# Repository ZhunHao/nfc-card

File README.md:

# NFC energy-harvesting business cards

Two battery-free PCB business cards. Tap one on a phone and its NFC field powers an
ATtiny1616 that animates 20 Charlieplexed red LEDs. There's no battery and no button.

The Orbit card on the back of an Android phone, running only on power harvested from the NFC
field: an ISS pass, the ground stations, then the 2,000 km pass.

The Terminal card hasn't been built yet, so these are the KiCad renders of both designs:

| C1 Orbit | B3 Terminal |
| --- | --- |
|  |  |
|  |  |

- **C1 Orbit**: Earth's limb, the ISS orbit (420 km) and the top of LEO (2,000 km) at true
  scale (1 mm ≈ 80 km). LEDs trace an ISS pass, light three ground stations, then run the
  2,000 km pass.
- **B3 Terminal**: a macOS Terminal window running `ping`. Each output line gets a status LED,
  and a progress bar fills along the bottom.

The phone number is left off the committed boards; see [Your own contact details](#your-own-contact-details).

## Inspiration and credit

This project is directly inspired by **Wilson Harper's
[NFC Energy-Harvesting PCB Business Card with an MCU](https://wilsonharper.net/projects/businesscard/)**
([repo](https://github.com/WiHarper/nfc-card)). His write-up showed that an NXP NTAG I2C Plus
can harvest enough power from a phone to run an ATtiny and Charlieplexed LEDs on a card-sized
board. Several decisions here follow his card directly:

- the **soft-start reservoir**: a large capacitor charged through a resistor, then switched
  in by a P-FET under MCU control, so VOUT stays inside the NTAG's 220 nF limit at start-up;
- a perimeter coil with **no ground plane** and LED routing that never closes a loop;
- **UPDI / VCC / GND pads at 0.1" pitch** on the back for a pogo-pin clip, with a TVS diode on
  UPDI, programmed with an Adafruit UPDI Friend;
- thin (≈ 0.8 mm) ENIG boards, assembled by JLCPCB.

Read his write-up first. It explains the core ideas better than this repo does. What this
repo adds is two new card designs on an ATtiny1616 (VQFN-20), scripted KiCad layouts,
interrupt-driven LED scanning with brown-out-aware power tiers, and a bring-up log that
includes iPhone behaviour.

## Hardware

| | |
| --- | --- |
| NFC / harvester | NXP NTAG I2C Plus NT3H2111 (VOUT energy harvesting) |
| MCU | Microchip ATtiny1616-MNR, VQFN-20 3 × 3 mm |
| LEDs | 20 × red 0603, Charlieplexed on 5 GPIOs, 100 Ω per line |
| Antenna | 4-turn perimeter coil, 0.50 mm gaps, tuned with the NTAG's 50 pF |
| Board | ID-1 (85.6 × 54 mm), 0.8 mm FR-4, 2 layers, black mask, ENIG |
| Programming | UPDI pads TP1–TP3 on the back (UPDI / VCC / GND, 2.54 mm pitch) |

The two cards share one circuit, and `scripts/check.sh` checks it: each schematic's netlist
must match `fab/reference/card-netlist.xml`.

**Status (2026-11):** Orbit has been built (JLCPCB order Y8) and brought up. On Android the
full animation runs on harvested power. iOS only powers the field in short polls, so an
iPhone tap gives a single LED blink and opens the URL. See
[docs/bringup](docs/bringup/2026-11-08-orbit-first-cards.md).

## Repository layout

```
hardware/   KiCad 10 projects (orbit/, terminal/), shared symbol + footprint library (lib/),
            and the Python builders that generate each board's placement, routing and silk
firmware/   bare-metal C for the ATtiny1616: shared core in src/, one animation per board in
            boards/, host tests in tests/, programming script in tools/
scripts/    checks (ERC/DRC/parity/netlist/coil loops/thickness), antenna generator, JLC
            DFM clean-up, fab export (single card and two-card panel)
sim/        LTspice decks and coil inductance estimates
docs/       design concepts, NFC tag setup, panel quotes, bring-up log
gallery/    photos of the built Orbit card and renders of both designs
```

## Build and check

You need KiCad 10 (`kicad-cli` and its bundled Python), Python 3, a host C compiler and
avr-gcc 14.3.0 (the version the ISR timing was audited against).

```bash
AVR_CC=/path/to/avr-gcc-14.3.0 ./scripts/check.sh
```

This runs ERC, DRC, schematic parity, board thickness, coil-loop and netlist checks for every
board under `hardware/`, plus the firmware host tests and AVR builds for every animation.

Regenerate a board after editing its builder (run it with KiCad's Python):

```bash
/Applications/KiCad/KiCad.app/Contents/Frameworks/Python.framework/Versions/Current/bin/python3 hardware/orbit/build_orbit.py
```

Export a JLCPCB package (gerbers, BOM, CPL with JLC rotation offsets, renders). It goes to
`fab/<board>-v2/`, which is not committed:

```bash
python3 scripts/export-card.py orbit
```

Flash a card over UPDI (Adafruit UPDI Friend plus a 0.1" pogo clip). See
[firmware/README.md](firmware/README.md):

```bash
firmware/tools/program-card.sh orbit-01
```

The NTAG is written from a phone (NFC Tools or NXP TagWriter). A blank NT3H2111 has to be
formatted first; see [docs/nfc-tag.md](docs/nfc-tag.md).

## Your own contact details

The card backs print a name, title, email and website. To keep a phone number out of the
repo, the committed boards leave it off, and the builders only add it when you pass a
private contact file:

```bash
cp contact.example.json contact.local.json   # gitignored; put your number in it
python3 scripts/export-card.py orbit --contact contact.local.json
```

That rebuilds a private copy under `build/personal/` and exports gerbers from that copy. The
boards under `hardware/` are not touched. To make the cards your own, change the name, email
and site in `hardware/*/build_*.py`.

## License

- Hardware (`hardware/`, `fab/reference/`, `sim/`):
  [CERN-OHL-S-2.0](LICENSES/CERN-OHL-S-2.0.txt)
- Firmware and scripts (`firmware/`, `scripts/`, `docs/design/data/`):
  [GPL-3.0-or-later](LICENSES/GPL-3.0-or-later.txt)

These are the licences of [Wilson Harper's card](https://github.com/WiHarper/nfc-card), which
inspired this one. See [LICENSE.md](LICENSE.md).

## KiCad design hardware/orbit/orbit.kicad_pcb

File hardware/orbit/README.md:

# C1 Orbit to scale

Earth's limb and two orbits at true scale on an ID-1 card: Earth R = 80 mm centred at
concept (43, 118), so 1 mm ≈ 79.64 km. ISS orbit r = 85.274 mm (420 km), upper orbit
r = 105.114 mm (2,000 km, top of LEO). Every arc, bus and LED is concentric with Earth.
Concept coordinates are mm from the card's top-left; KiCad = concept + 100.

Rev B electronics: the
NTUAS circuit with U2 as ATtiny1616-MNR (VQFN-20 3 × 3 mm), a UPDI ESD diode D21, a soft-start
reservoir (Q1, R7, R8, C4), test pads on the back and antenna option A. U1, C1, C2 and the U1
end of the LA/LB routing are the NTUAS card's; the LA feed to the coil is rebuilt (see Routing).
Everything else on the board is generated by `build_orbit.py` (KiCad 10 Python, idempotent):

```bash
/Applications/KiCad/KiCad.app/Contents/Frameworks/Python.framework/Versions/Current/bin/python3 hardware/orbit/build_orbit.py
```

## LED mapping

LED index k is D[k+1]: anode CP[k/4], cathode CP[c], c = (k%4) < (k/4) ? k%4 : k%4+1.
Positions are listed left to right. `firmware/boards/orbit/animation.c` uses the same order.

| Row | x (concept mm) | Ref (index k) |
| --- | --- | --- |
| ISS, r 85.274 | 12, 19.8, 27.6, 35.4, 43.2, 51, 58.8, 66.6, 74.4 | D2 (1), D3 (2), D1 (0), D4 (3), D6 (5), D7 (6), D8 (7), D5 (4), D9 (8) |
| 2,000 km, r 105.114 | 11, 19.5, 28, 36.5, 45, 53.5, 62, 70.5 | D10 (9), D13 (12), D14 (13), D15 (14), D17 (16), D18 (17), D19 (18), D20 (19) |
| Ground stations, limb + 2.6 | 27.6, 43, 66 | D11 (10), D16 (15), D12 (11) |

The station LEDs sit under the ISS LEDs at x = 27.6, 43.2 and 66.6, which light them in the animation.

## Deviations from the concept

- **Ground station x = 20 moved to x = 27.6** (still on the limb, 2.6 mm inside it). At x = 20 it
  landed on U1/C2 at the antenna feed. 27.6 puts it under an ISS LED like the other two.
- All LEDs are rotated tangent to their orbit (concept draws them axis-aligned).
- Labels are raised from 0.95 to 1.0 mm (JLCPCB standard minimum, 0.15 mm stroke) in KiCad's
  stroke font, not JetBrains Mono. Letter spacing is not available except for `E A R T H`,
  which is set letter by letter. `ISS · 420 km` starts at x = 43.5 (concept 47) to stay off the
  routing trunk; `2,000 km · TOP OF LEO` sits 2.4 mm above its arc (concept 1.4) because the
  wider stroke font would otherwise cover the LEDs at x = 36.5 and 45.
- **LED cathode dots** (after order Y8): a 0.4 mm silk dot beside each LED's pad 1 (the
  cathode), on the side away from its bus stubs (outward on the ISS row, inward on the
  2,000 km row and the stations), 0.27 mm clear of the pad. The library LED outline sits
  0.1 mm from the pads, so the 0.25 mm silk cut-back removed it and Y8 shipped with no LED
  polarity mark, which led JLC to ask for a polarity check. A dot past the pad end would land
  on the orbit line and look like an orbit dot. The station chevrons are 0.35 mm lower than
  the concept (tip 1.2 mm below the LED centre) to clear the dots.
- Silk lines are all ≥ 0.15 mm. The concept's faint 0.09 mm rings and meridians are drawn
  dashed at 0.15 mm instead of at reduced opacity. Silk stops 0.25 mm short of pads.
- MCU block (concept mm): U2 (VQFN-20) at (69.5, 23.0), 90°, pin 1 bottom-left. R1–R5 stay in a
  column at x = 61.8 by the trunk (y = 23.8 … 27.8, PA1 … PA5). C3 sits under U2's VCC/GND pins at
  (69.7, 26.7), JP1 at (61.2, 30.6), R6 above U2 at (66.7, 20.6). The soft-start sits right of U2:
  R8 (74.2, 21.3), R7 (74.2, 22.3), Q1 (73.9, 23.6), C4 (72.75, 22.6). `LIFT JP1 TO FLASH` from
  the NTUAS card is dropped; JP1 is labelled.
- **Test pads on the back** (rev B): TP1/TP2/TP3 (**UPDI / VCC / GND**, VCC in the middle) are
  1.5 mm pads on B.Cu in a vertical column at 2.54 mm pitch, x = 77.5, y = 7.8 / 10.34 / 12.88,
  for a 0.1" pogo clip. Seen from the back they sit top-left, above the name, with mirrored
  B.SilkS labels (1.0 mm tall, 0.8 mm glyphs) aligned with the contact block. Each pad is fed by
  a via 1.25 mm to its left, never in the pad. The front TP labels are gone.
- D21 (UPDI TVS) sits on the front directly behind TP1, at (77.55, 8.25); its GND pad runs down
  to TP3's via.
- Back: `TAP TO CONNECT` and its glyph moved 2 mm toward the centre to clear the antenna band.
- Back: the two TLE lines keep the 1.0 mm height but use 0.62 mm-wide glyphs, so they run
  about 39 mm like the concept's monospace (37.6 mm) instead of 62 mm. JLC's line gap is still met.

## Routing

Each orbit row has five concentric B.Cu bus arcs, one per Charlieplex net (ISS buses inside the
ISS row, 2,000 km buses outside its row, pitch 0.85 mm). Every LED pad drops a short radial F.Cu
stub to a via on its net's bus. One radial F.Cu trunk (through the ISS orbit at x = 55, between
LEDs) joins both bus sets; B.Cu branches tap it to R1–R5. The stations share the ISS buses: the
ISS LED above each station only uses buses outside both of the station's, so their stubs never
meet. VOUT and GND leave U1/C2 on B.Cu arcs inside Earth (r ≈ 78 and 76.5 mm) and ride the trunk
up to JP1 and the MCU. No autorouter was used; DRC (error severity) is clean with no unconnected
items and no parity issues.

**MCU block fan-out (VQFN-20, 0.4 mm pitch).** Escapes are 0.15 mm straight out of each pad.
PA1 (pin 20, left side) and PA2/PA3 (pins 1/2, bottom side) run to R1–R3 on F.Cu as nested
L-shapes. PA4/PA5 (pins 5/6) drop to vias beside the package and pass under the block on B.Cu to
vias next to R4/R5. GND (pin 3) is tied to the exposed pad by a short track inside the body
(no ground plane on this card) and, with VCC (pin 4), runs straight down into C3. UPDI (pin 19)
goes up through R6 and over the top of U2; SS_GATE (pin 15) runs alongside to R8 and Q1's gate.
VCC goes JP1 → C3 → a spine up the right side to TP2, with the soft-start parts and Q1's source
stubbed onto it. GND runs on B.Cu directly under that VCC rail and spine (a broadside pair, so
the VCC/GND loop closed by C3 and C4 encloses almost nothing) up to TP3, with a branch to C4.

**Antenna feed (option A).** The new coil's outer pad (LA) is at (120.0, 151.53) and its inner
pad (LB) at (114.4, 147.33), KiCad mm. The NTUAS LA via at (120.0, 150.7) would sit inside coil
turn 2 (same net, so DRC is silent, but it bypasses part of the coil), so it is gone: LA leaves
U1 as before, runs down B.Cu at x = 115.8 to y = 152.9 (outside the coil), across to a via at
(120.0, 152.9) and back up F.Cu to the pad. LB drops from (114.7, 146.58) to its pad at
(114.4, 147.33). The builder rebuilds the whole LA/LB set each run. The coil band is wider now
(2.0–7.1 mm from the edge, was ~3.8–6.5 on NTUAS). Widening the gaps to 0.50 mm (2026-10-27)
moved the inner edge from 6.5 to 7.1 mm, but no LED, bus or silk moved: the closest other-net
F.Cu copper is the TP1 via at (176.25, 107.8), about 0.4 mm away. TP1–TP3 themselves are on
B.Cu, under the inner turn.

## Manufacturing notes

Same as the NTUAS card: black
mask, ENIG, top-side assembly, but **0.8 mm** thick (NTUAS: 1.0 mm); set PCB Thickness to 0.8
in the JLC quote. **36 fitted parts** (the NTUAS 31 plus D21, Q1, R7, R8,
C4); C1 (not fitted), L1 (copper) and TP1–TP3 (bare pads on the back) are not assembled. U2 is
the VQFN-20 ATtiny1616-MNR (LCSC C507118) at 90° here. `scripts/export-card.py` corrects U2
(-90°) and Q1 (180°) for JLC's library, as checked on the Terminal card in JLCONE on 2026-10-28.
Orbit's own placement preview was checked the same day (see Ordering below).

Physical validation (NFC range, LED brightness, harvested power) is still unproven on the NTUAS
card and inherited here.

## Ordering (JLCPCB)

The first batch (Y8, 2026-10-28) was 20 PCBs with 15 assembled, about US$141 before shipping.

- **PCB:** 0.8 mm FR-4, black mask, ENIG, 1 oz, tented 0.3 mm vias, order number removed,
  Confirm Production File on.
- **Assembly:** Standard PCBA, top side, JLC adds and removes the edge rails, Confirm Parts
  Placement on. Upload the `bom.csv` and `cpl.csv` from `scripts/export-card.py`, which already
  apply the U2 and Q1 rotation offsets.
- **Placement preview:** every LED needs JLC's "−" on pad 1 (the cathode); U1, U2 and Q1 need
  their pin-1 dots on pad 1. D21 is bidirectional.
- Y8 had no LED polarity marks (see "LED cathode dots"), so JLC's engineer revised the LED
  placement and asked for a polarity check. The current boards have the marks.
- Approve the placement within 72 h (JLC auto-confirms after that), then flash the firmware
  over TP1–TP3.

## Bring-up (2026-11-08)

Full log: `docs/bringup/2026-11-08-orbit-first-cards.md`.

- **R6 is too high for the UPDI Friend.** With R6 = 4.7 kΩ the chip's reply never pulls the
  Friend's line (1 kΩ pull-up) below about 2.7 V, so avrdude fails at link initialization. Bridge
  R6 to program; it can stay bridged (D21 still clamps TP1). **Fixed in the design
  (2026-11-08): R6 is now 0 Ω** (UNI-ROYAL 0402WGF0000TCE, LCSC C17168, JLC basic) in the
  schematic, the board and `fab/reference/card-netlist.xml`. No resistor is needed on the card: the UPDI Friend already has 1 kΩ in series with its TX, it powers the card from the same 3 V supply, and D21 clamps static on TP1. Every setup known to work has none (R6 bridged on Y8, Wilson Harper's card).
  470 Ω (SpenceKonde's value for programmers that drive UPDI directly) was tried first
  and dropped untested: a divider estimate put the low level near 1.1 V against the
  Friend's 1 kΩ. The 0402 pads stay, so a resistor can be fitted for another programmer.
  Only future orders get it: the 15 assembled Y8 cards have 4.7 kΩ and still
  need R6 bridged.
- On card 2 with R6 bridged: signature `0x1e9421`, fuses set, all 20 LEDs and the Orbit
  animation verified on 3.3 V programmer power. The tag still reads with JP1 fitted.
- Harvested power starts the MCU and passes the VLM check with the card on the back of an
  iPhone, without C1. The iPhone field lasts only about 30–65 ms per tap, so the animation
  (100 ms qualification, 800 ms fade-in) does not show there; firmware now flashes D16 at
  power-up so each iPhone poll gives a blink. On Android the full animation runs.
- Card 1 was reverse-powered several times by a cable whose colours differ from Adafruit's
  guide, and has not been rechecked.

## Pre-order checks (2026-10-26)

Estimates and design-file checks only. None replaces tapping a phone on an assembled card.

**Antenna (rev B: option A).** L1 is now `nfc-card:NFC_Antenna_Rect_ID1_4turn_W090`: 4 turns
at a 2.0 mm inset, 0.90 mm track, **0.50 mm gap** (1.40 mm pitch). FastHenry
(`sim/fasthenry_coil.py`, skin effect resolved) gives **2.37 µH at 13.56 MHz**, so 14.63 MHz at
the NTAG's 50 pF (13.82–15.59 MHz over 44–56 pF), aiming high so C1 (not fitted) can tune it
down after a NanoVNA check: 14.41 / 14.17 / 13.87 MHz with C1 = 1.5 / 3.3 / 5.6 pF. Area ×
turns is 138 cm². Until 2026-10-27 the gap was 0.30 mm on AN11276's 2.39 µH, but FastHenry gives
that coil 2.49 µH: 14.26 MHz at 50 pF and 13.48 MHz at 56 pF, under the carrier with no fix,
since C1 only lowers it. `sim/coil_inductance.py` (Neumann integrals over the routed copper)
agrees, 2.388 µH at low frequency against FastHenry's 2.368 µH at 13.56 MHz. Board parasitics are
not in either number and will pull the frequency down a little. The NTUAS coil's estimate below is kept for reference:
Mohan et al. (IEEE JSSC 34(10), 1999), 77.6 × 45.98 mm outer, 4 turns, 0.35/0.35 mm: modified
Wheeler 2.41 µH → 14.49 MHz, current sheet 2.84 µH → 13.35 MHz, which could sit under 13.56 MHz.

**Copper inside the coil.** `scripts/check_loops.py` (run by `check.sh`) finds no closed copper
loop in any of the 19 routed nets on rev B. The supply loops close through capacitors, which are
near-shorts at 13.56 MHz. The always-closed C2 → JP1 → C3 loop encloses 30.6 mm² (rev A:
36.7 mm²), about 0.9 % of a mean rev B coil turn (~3,500 mm²). The largest supply loop is
C4 → Q1 → JP1 → U1 at 45.6 mm², closed once the firmware turns Q1 on. The gate fails any
supply loop over 100 mm². Lit-LED drive loops reach 102.8 mm² (D3), but an off LED is open at
RF and a lit one has about 400 Ω in series, so they are reported, not gated. The upper B.Cu bus
is 1.6 mm inside the innermost turn at its closest.

**Harvest power budget, LTspice** (`sim/harvest*.cir`). NTAG VOUT is modelled as a current source
clamped near 3.3 V (NXP datasheet Vout,max). C2 + C3 = 200 nF. The MCU is a 0.6 mA load, which is
pessimistic: the datasheet gives 8 MHz active at 3 V as 2.2 mA typical, 3.5 mA max, so 1 MHz scales
to about 0.3–0.45 mA. Each GPIO is 100 Ω (assumed; Microchip publishes only curves). The scan pulse
is the firmware's 62 µs per 250 µs slot. The LED model is fitted to KT-0603R at 2.0 V (typ) and
2.4 V (max) at 20 mA. Minimum VCC with at most two LEDs lit, as this animation runs:

| Harvested current | 0.3 mA | 0.5 mA | 0.75 mA | 1 mA | 2 mA | 5 mA |
| --- | --- | --- | --- | --- | --- | --- |
| VCC min, typical LED | 1.00 V | 1.61 V | 2.06 V | 2.41 V | 2.66 V | 3.21 V |
| VCC min, 2.4 V LED | 1.00 V | 1.66 V | 2.25 V | 2.61 V | 2.86 V | 3.24 V |
| LED peak current, typical | – | 0.2 mA | 2.0 mA | 3.5 mA | 3.7 mA | 3.8 mA |

Rev B adds the soft-start reservoir (C4 10 µF behind R7 2.2 kΩ, bypassed by Q1 once the
firmware latches it), which these 200 nF runs do not model; see `sim/vout_reservoir.cir` at the
repo root for its effect on ripple, hold-up and startup.

BODLEVEL0 is 1.7–2.0 V, so the card needs about **0.75–1 mA** from the phone to run. NXP's
typical figure is 5 mA at 2 V; the MCU, not the LEDs, dominates the load. Even with every slot
lit (`harvest.cir`), 1.5 mA holds VCC at or above 2.5 V.

**Brightness is the weaker margin.** The fixed scan gave each LED one 250 µs slot per 5 ms frame
at 62 µs on (1.25 % duty), about 20–46 µA from 2–3.8 mA peaks. Orbit and Terminal now use shared
slots (`firmware/docs/timing.md`): the lit LEDs share 6 slots, so one lit LED is on 7.4 % of the
time (about 150–280 µA) and two are on 3.7 % each (about 75–140 µA). Six lit slots is well under
the every-slot-lit case above. Whether that reads as clearly lit can only be judged on a real card.

**Gerbers (rev A export; redo for rev B).** The zip re-read: 9 layers plus a job file, 1.0 mm, 2 layers, 85.65 × 54.03 mm
including the outline stroke. The drill file has 69 × 0.3 mm holes, matching the 69 vias. B.Mask
and B.Paste are empty (single-sided). Rev B has 76 vias and opens B.Mask for the three test
pads, so these counts change at the next export. `scripts/jlc_dfm.py` (run before saving) widens all
silkscreen, library outlines included, to 0.16 mm, cuts it back 0.25 mm from every pad and hole,
gives U1/U2/Q1 a 0.02 mm mask margin and every via a 0.65 mm pad. The UPDI run over R6 moved up
0.2 mm (concept y 19.4) to clear R6's mask opening. JLCDFM (2026-10-28) then reports no danger or
warning items on the PCB; the SMT notes are as on Terminal (see its README).

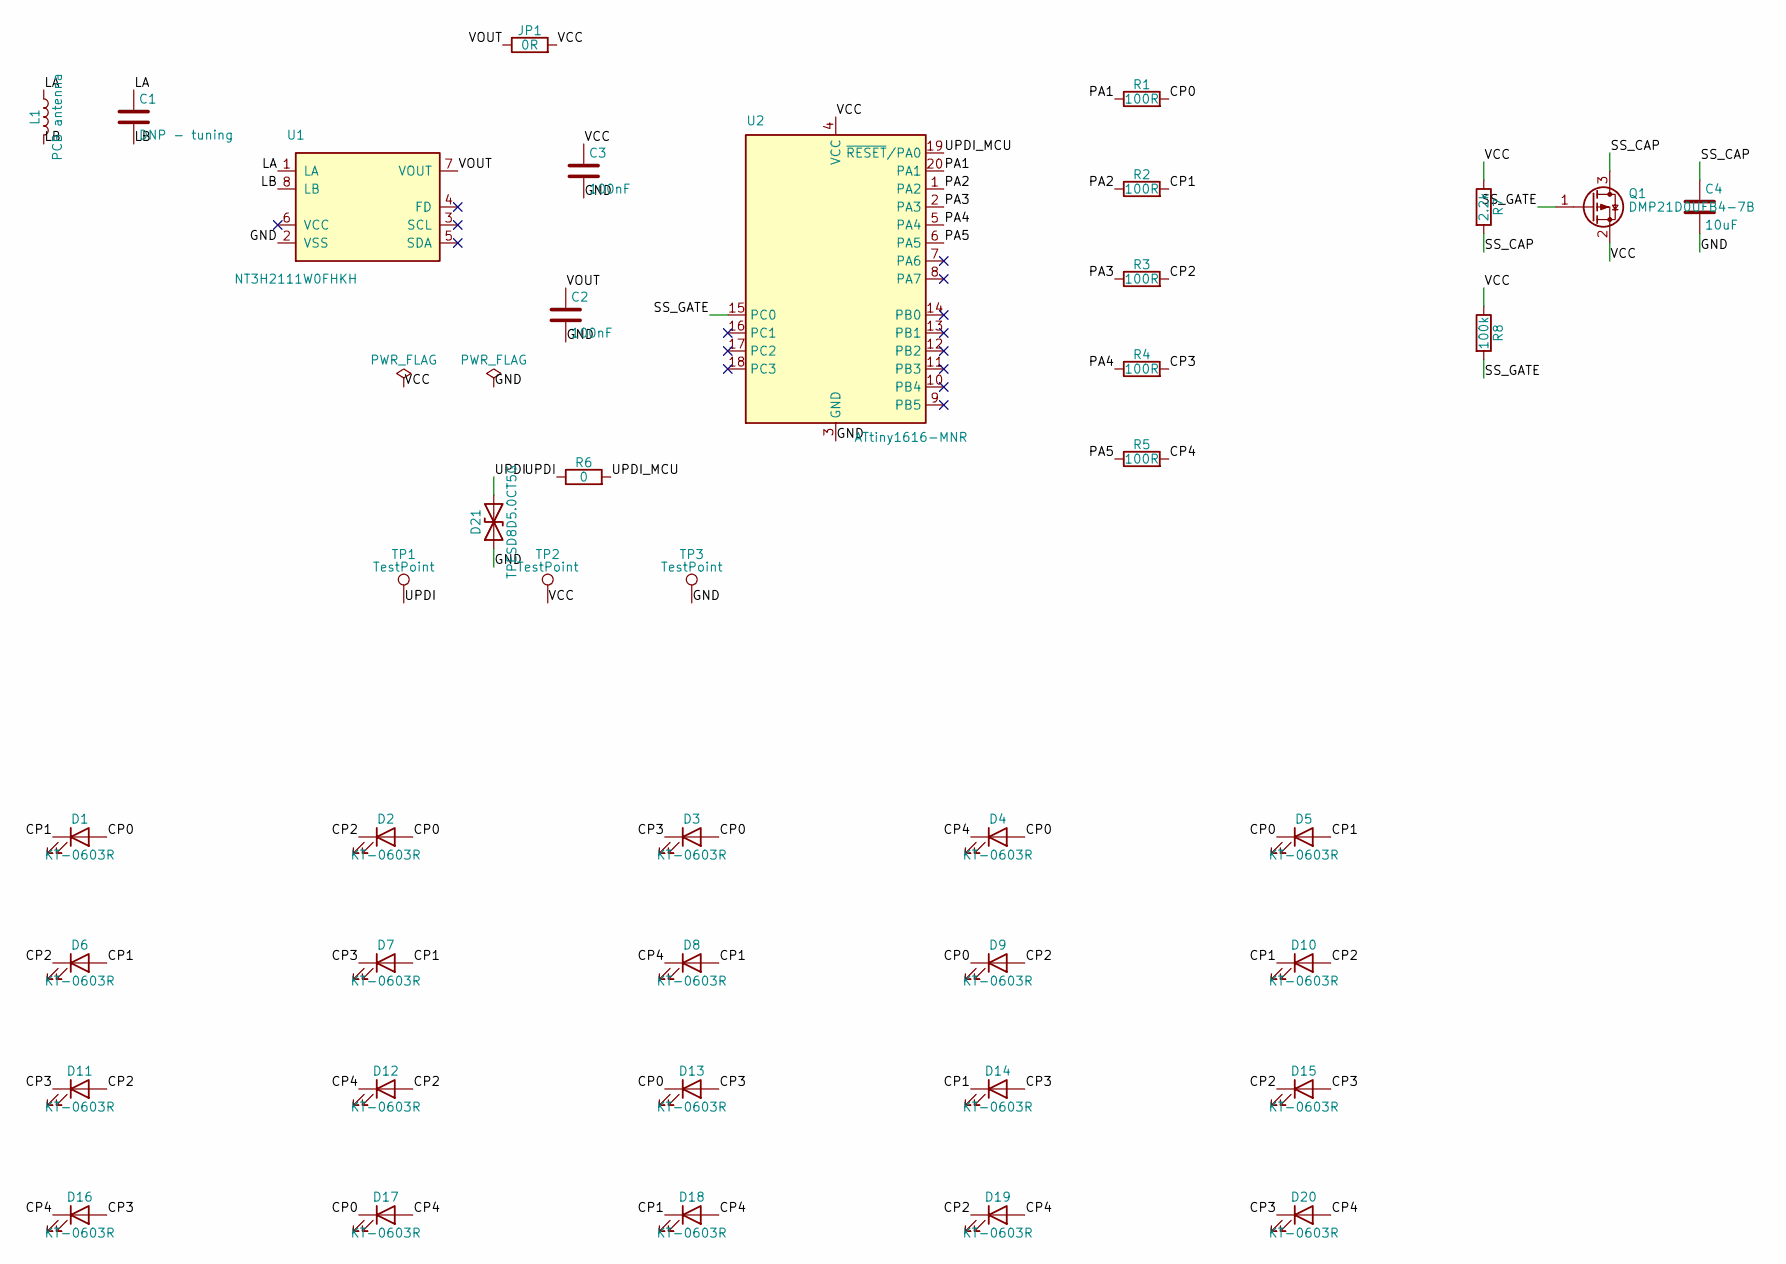
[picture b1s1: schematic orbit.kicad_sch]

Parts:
C1: DNP - tuning; C_0402_1005Metric
C2, C3: 100nF; C_0402_1005Metric; LCSC C1525
C4: 10uF; C_0402_1005Metric; LCSC C15525
D1, D2, D3, D4, D5, D6, D7, D8, D9, D10, D11, D12, D13, D14, D15, D16, D17, D18, D19, D20: KT-0603R; LED_0603_1608Metric; LCSC C2286
D21: TPESD8D5.0CT5G; D_SOD-882; LCSC C2827720
JP1: 0R; R_0603_1608Metric; LCSC C21189
L1: PCB antenna; NFC_Antenna_Rect_ID1_4turn_W090
Q1: DMP21D0UFB4-7B; Diodes_DFN1006-3; LCSC C155329
R1, R2, R3, R4, R5: 100R; R_0402_1005Metric; LCSC C25076
R6: 0; R_0402_1005Metric; LCSC C17168
R7: 2.2k; R_0402_1005Metric; LCSC C25879
R8: 100k; R_0402_1005Metric; LCSC C25741
TP1, TP2, TP3: TestPoint; TestPoint_Pad_D1.5mm
U1: NT3H2111W0FHKH; XQFN-8_1.6x1.6mm_P0.5mm_NXP_SOT902-3; LCSC C710403
U2: ATtiny1616-MNR; QFN-20-1EP_3x3mm_P0.4mm_EP1.65x1.65mm; LCSC C507118

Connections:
/CP0: D1.2 (A), D2.2 (A), D3.2 (A), D4.2 (A), D5.1 (K), D9.1 (K), D13.1 (K), D17.1 (K), R1.2
/CP1: D1.1 (K), D5.2 (A), D6.2 (A), D7.2 (A), D8.2 (A), D10.1 (K), D14.1 (K), D18.1 (K), R2.2
/CP2: D2.1 (K), D6.1 (K), D9.2 (A), D10.2 (A), D11.2 (A), D12.2 (A), D15.1 (K), D19.1 (K), R3.2
/CP3: D3.1 (K), D7.1 (K), D11.1 (K), D13.2 (A), D14.2 (A), D15.2 (A), D16.2 (A), D20.1 (K), R4.2
/CP4: D4.1 (K), D8.1 (K), D12.1 (K), D16.1 (K), D17.2 (A), D18.2 (A), D19.2 (A), D20.2 (A), R5.2
/GND: C2.2, C3.2, C4.2, D21.1 (A1), TP3.1 (1_1), U1.2 (VSS), U2.3 (GND), U2.21 (GND)
/LA: C1.1, L1.1, U1.1 (LA)
/LB: C1.2, L1.2, U1.8 (LB)
/PA1: R1.1, U2.20 (PA1)
/PA2: R2.1, U2.1 (PA2)
/PA3: R3.1, U2.2 (PA3)
/PA4: R4.1, U2.5 (PA4)
/PA5: R5.1, U2.6 (PA5)
/SS_CAP: C4.1, Q1.3 (D), R7.2
/SS_GATE: Q1.1 (G), R8.2, U2.15 (PC0)
/UPDI: D21.2 (A2), R6.1, TP1.1 (1_1)
/UPDI_MCU: R6.2, U2.19 (~RESET/PA0)
/VCC: C3.1, JP1.2, Q1.2 (S), R7.1, R8.1, TP2.1 (1_1), U2.4 (VCC)
/VOUT: C2.1, JP1.1, U1.7 (VOUT)

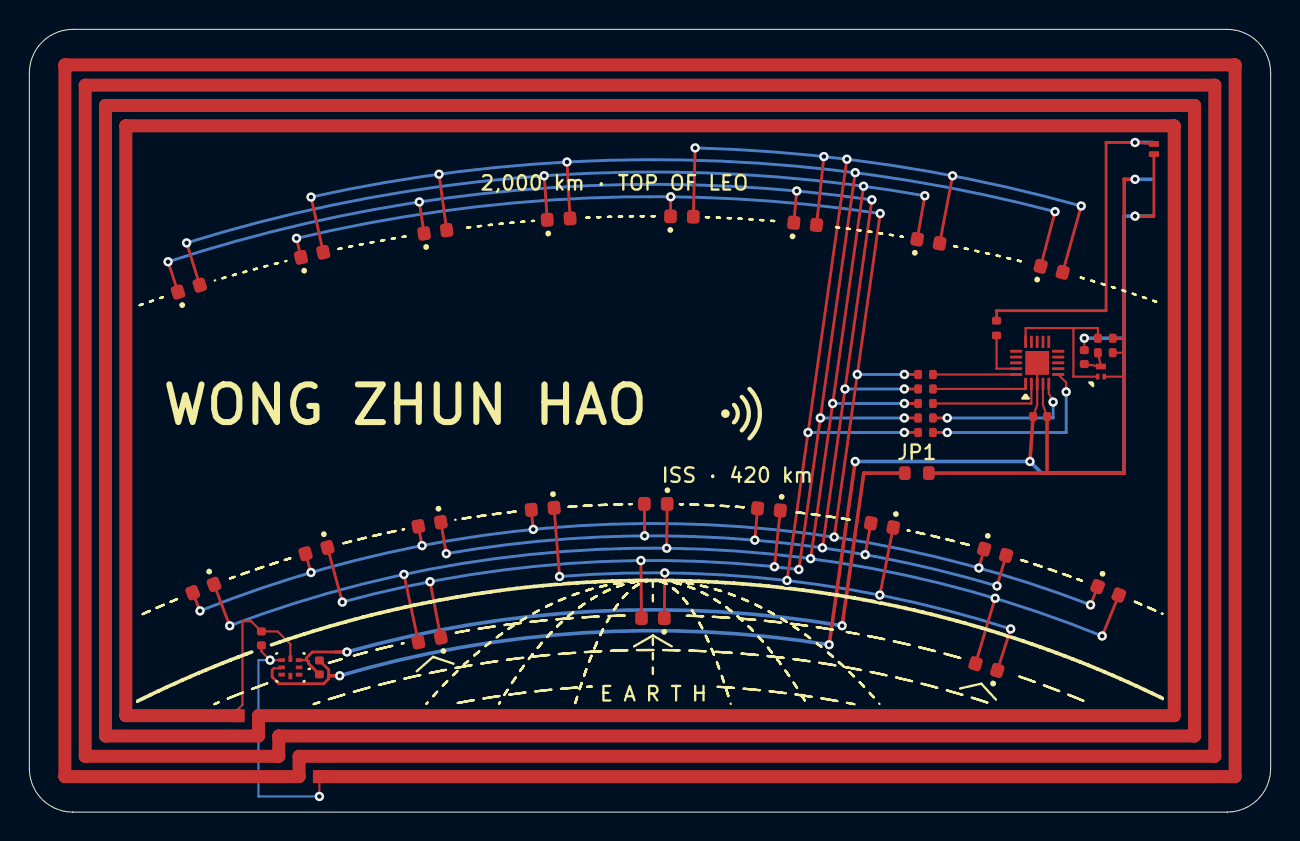
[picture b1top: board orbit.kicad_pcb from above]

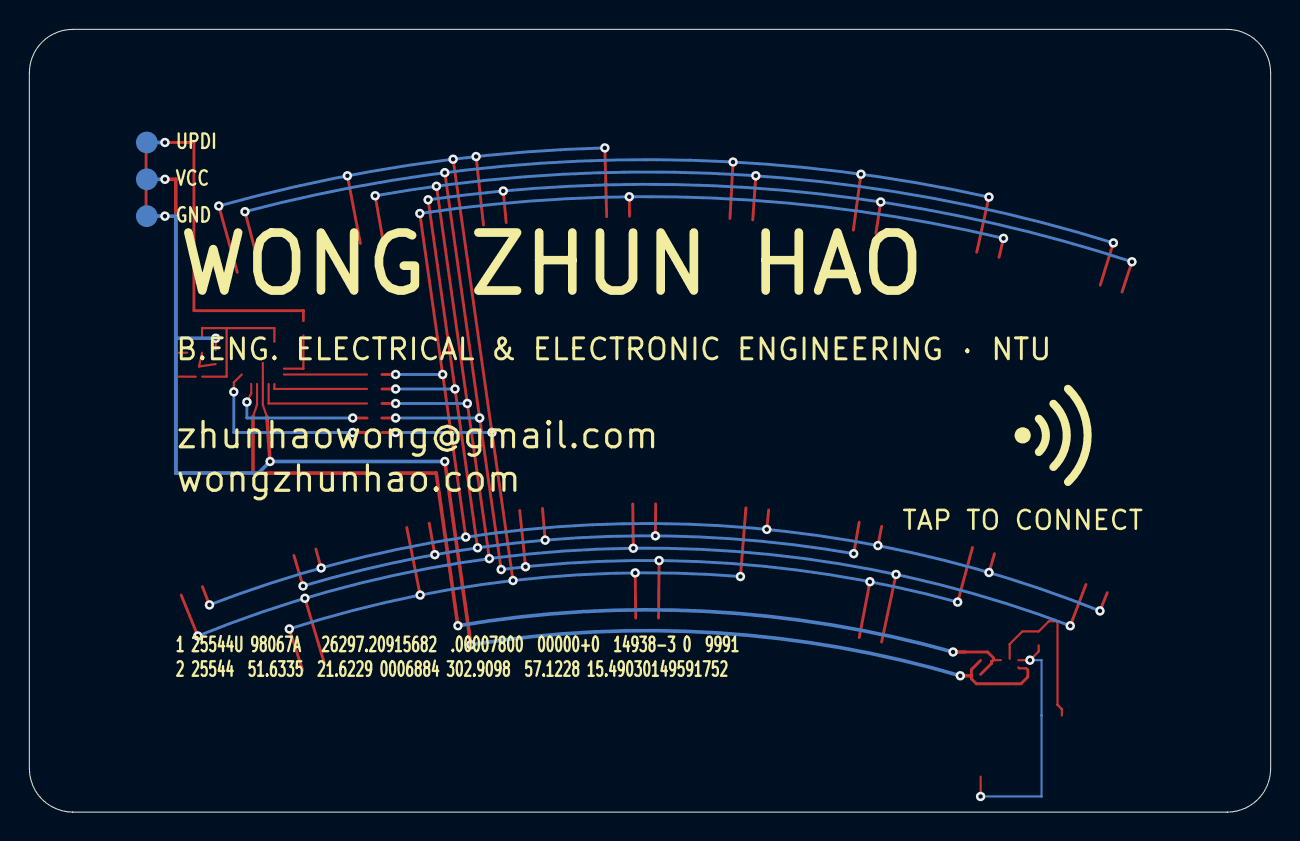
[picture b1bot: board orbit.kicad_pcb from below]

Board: 2 copper layers, 85.6 x 54.0 mm, 41 parts (3 on the bottom side), 19 nets.

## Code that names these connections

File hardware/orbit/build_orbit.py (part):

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Charlieplex routing, the power runs, the back test pads and all silkscreen.

Rev B MCU block (concept mm, U2 = ATtiny1616 VQFN-20 at 90 deg, pin 1
bottom-left): PA1 leaves the left side and PA2/PA3 the bottom side straight to
R1-R3 on F.Cu; PA4/PA5 drop to vias and run under the block on B.Cu to R4/R5.
VCC and GND leave the bottom side into C3 (EP tied to pin 3 inside the body).
UPDI (via R6) and the soft-start's SS_GATE cross over the top; Q1/R7/R8/C4
sit right of U2 against a VCC spine that climbs to the back test pads.
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
U2_AT = (69.5, 23.0)                 # VQFN-20, 90 deg: pins 1-5 along the bottom
R_X = 61.8
R_Y = {'R1': 23.8, 'R2': 24.8, 'R3': 25.8, 'R4': 26.8, 'R5': 27.8}   # PA1..PA5
JP1_AT, C3_AT = (61.2, 30.6), (69.7, 26.7)
R6_AT = (66.7, 20.6)                 # UPDI series resistor, above U2
SS_AT = {'R8': ((74.2, 21.3), 180), 'R7': ((74.2, 22.3), 180),
         'Q1': ((73.9, 23.6), 90), 'C4': ((72.75, 22.6), 90)}
PA4_VIA, PA5_VIA = (70.6, 25.7), (71.5, 25.0)
PA_NEAR_X = 63.3                     # B.Cu PA4/PA5 surface next to R4/R5
SS_GATE_Y, SS_GATE_X = 20.6, 72.0
UPDI_Y, UPDI_X = 19.4, 74.25         # UPDI over the top, then up to TP1
VCC_X = 75.5                         # VCC spine up the right side to TP2
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# middle. Each pad's via sits 1.25 mm to its left, never in the pad.
TP_X, TP_VIA_X = 77.5, 76.25
TP_Y = {'TP1': 7.8, 'TP2': 10.34, 'TP3': 12.88}   # GND label clears the back name
TP_LABEL = {'TP1': 'UPDI', 'TP2': 'VCC', 'TP3': 'GND'}
D21_AT = (77.55, 8.25)               # front, behind TP1; GND runs down to TP3's via
VCC_Y, VOUT_Y, GND_BRANCH_Y = 30.6, 30.6, 29.8
U1_VOUT_NODE, U1_VOUT_VIA = (21.112, 42.937), (21.9, 42.937)
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    place_back(ref, (TP_X, y))

# The routing below relies on this pinout (ATtiny1616 VQFN-20 and friends).
EXPECT = {('U2', '1'): '/PA2', ('U2', '2'): '/PA3', ('U2', '3'): '/GND', ('U2', '4'): '/VCC',
          ('U2', '5'): '/PA4', ('U2', '6'): '/PA5', ('U2', '15'): '/SS_GATE',
          ('U2', '19'): '/UPDI_MCU', ('U2', '20'): '/PA1', ('U2', '21'): '/GND',
          ('R1', '1'): '/PA1', ('R2', '1'): '/PA2', ('R3', '1'): '/PA3', ('R4', '1'): '/PA4',
          ('R5', '1'): '/PA5', ('R6', '1'): '/UPDI', ('R6', '2'): '/UPDI_MCU',
          ('C3', '1'): '/VCC', ('C3', '2'): '/GND', ('JP1', '1'): '/VOUT', ('JP1', '2'): '/VCC',
          ('Q1', '1'): '/SS_GATE', ('Q1', '2'): '/VCC', ('Q1', '3'): '/SS_CAP',
          ('R7', '1'): '/VCC', ('R7', '2'): '/SS_CAP', ('R8', '1'): '/VCC', ('R8', '2'): '/SS_GATE',
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u2 = lambda n: pad_xy('U2', str(n))
W_ESC = 0.15                         # QFN escapes: 0.2 mm pads on 0.4 mm pitch

# PA1 (left side) and PA2/PA3 (bottom side) straight to R1-R3 on F.Cu.
path([u2(20), pad_xy('R1', '1')], '/PA1', W_ESC)
for pin, ref in ((1, 'R2'), (2, 'R3')):
    pa = pad_xy(ref, '1')
    path([u2(pin), (u2(pin)[0], pa[1]), pa], pad_net(ref, '1'), W_ESC)
# PA4/PA5 drop to vias and pass under the block on B.Cu.
for pin, ref, v, mid in ((5, 'R4', PA4_VIA, (u2(5)[0], 25.1)),
                         (6, 'R5', PA5_VIA, (71.5, 24.35))):
    name, pa = pad_net(ref, '1'), pad_xy(ref, '1')
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     '/VCC', W_PWR)
track((c3_vcc[0], VCC_Y), c3_vcc, '/VCC', W_PWR)

# UPDI: pin 19 -> R6 above U2 -> over the top -> up to TP1's via -> D21.
r6_mcu, r6_tp = pad_xy('R6', '2'), pad_xy('R6', '1')
path([u2(19), (r6_mcu[0], u2(19)[1]), r6_mcu], '/UPDI_MCU', W_ESC)
path([r6_tp, (r6_tp[0], UPDI_Y), (UPDI_X, UPDI_Y), (UPDI_X, TP_Y['TP1']), tp_via['TP1']], '/UPDI')
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d21_gnd = pad_xy('D21', '1')
path([d21_gnd, (d21_gnd[0], TP_Y['TP3']), tp_via['TP3']], '/GND', W_SIG)

# Soft-start: SS_GATE over the top to R8 and Q1's gate; VCC stubs to the spine.
gate = pad_xy('Q1', '1')
r8_gate = pad_xy('R8', '2')
path([u2(15), (u2(15)[0], SS_GATE_Y), (r8_gate[0], SS_GATE_Y), r8_gate], '/SS_GATE', W_ESC)
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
